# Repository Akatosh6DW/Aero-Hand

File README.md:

<p align="center">

  <!--  -->

</p>

Aero Hand Open is an **open-source**, **tendon-driven** robotic hand designed and developed by TetherIA for dexterous manipulation research. Unlike expensive proprietary solutions, this hand focuses on **simplicity**, **reliability**, and **accessibility** by using standard 3D printing and off-the-shelf electronic components.

Each joint is optimized for mechanical efficiency through tendon actuation, enabling smooth and natural motion while maintaining a **lightweight** and **compact** design, making it perfect for research labs, educational institutions, and robotics enthusiasts who need an **affordable** yet **capable** manipulation platform.

> **📚 Learn More:** https://tetheria.github.io/aero-hand-open/   
> **🛒 Shop:** https://shop.tetheria.ai/

# Aero Hand Open features
- 7 DoFs robotic hand with 5 fingers (16 joints in total)
- Tendon-driven architecture for smooth and natural motion
- Fully 3D-printed structure, modular and easy to assemble
- Lightweight design — **389 g**
- Affordable — complete kit for **$314 USD**
- Open-source hardware and firmware
- Independent Python SDK, and compatible with ESP32 and ROS2 systems

# Table of Contents
- [Aero Hand Open features](#aero-hand-open-features)
- [Overview](#overview)
- [Resources](#resources)
  - [Bill of Materials (BOM)](#bill-of-materials-bom)
  - [CAD Files and 3D Models](#cad-files-and-3d-models)
  - [Assembly Guide](#assembly-guide)
  - [PCB Design](#pcb-design)
  - [Hardware Setup](#hardware-setup)
  - [Software SDK](#software-sdk)
  - [ROS2 and Teleoperation](#ros2-and-teleoperation)
  - [Simulation](#simulation)
  - [Reinforcement Learning](#reinforcement-learning-tools)
- [Getting help](#Getting-help)
- [License — TL;DR](#license--tldr)
- [Disclaimer](#disclaimer)
- [Project Updates & Community](#project-updates--community)
  - [Updates History](#updates-history)
  - [FAQ](#faq)
  - [Contact](#contact)

# Overview

# Resources
## Bill of Materials (BOM)
The complete list of components required to build Aero Hand Open can be found here:

 [👉 Aero Hand Open – Bill of Materials](./hardware/Assembly/BOM.csv)

This document includes all mechanical, electronic, and printed parts — such as motors, tendons, bearings, fasteners, and 3D-printed components.

Each item is listed with its part number, vendor, quantity, and estimated cost to help you easily source or substitute parts.

## CAD Files and 3D Models
STEP files and one click print files can be found here:

[👉 Aero Hand Open – CAD](./hardware/CAD/).

[👉 Aero Hand Open – Onshape Link](https://cad.onshape.com/documents/afc7e0ca7eb6d412ec8771f8/w/bc4d7e45e17e23d622d2bad2/e/c711982b7882da925263fb55?renderMode=0&uiState=6914cef580110c73012e8166)

All parts are printed on a Bambu X1C, 0.4mm nozzle, 0.2mm layer height, tree support enabled, select support on build plate only checkbox. We recommend keeping the same print orientation and settings. The print orientation will minimize supports and optimize surface tolerances/smoothness for interfacing components.

## Assembly Guide
The step-by-step assembly instructions for Aero Hand Open are provided in the following document:

[👉 Aero Hand Open – Assembly Guide](https://docs.tetheria.ai/docs/assembly)

This guide covers the entire build process, from mounting the actuators to routing the tendons and connecting the electronics. Each finger module can be assembled independently and attached to the palm afterward, allowing easier maintenance and quick replacement.

## PCB Design
All design files - including Gerber files, KiCad project files, BOM, and CPL - are available in [PCB folder](./hardware/PCB/).

Referring to [PCB doc](https://docs.tetheria.ai/docs/pcb) for more technical details.

## Hardware Setup

Please refer to [hardware_setup](https://docs.tetheria.ai/docs/hardware_setup) doc 

## Software SDK
Please refer to [`sdk/README.md`](sdk/README.md) and [sdk](https://docs.tetheria.ai/docs/sdk) doc

### Sequencing Demo
The Sequencing Demo demonstrates how different finger motions can be combined into continuous, pre-defined sequences.

This script enables users to perform complex gestures — such as pinching, opening the palm, or making a peace sign — by automatically coordinating joint movements in a timed sequence.

You can find the example code in the SDK example folder. 

👉 [`sdk/examples/`](sdk/examples)

Once the SDK is installed and the serial port has been configured, you can run any of the example scripts directly using Python as follows:

```bash
python run_sequence.py
```
[🎥 Watch the demo](assets/sequence_square.mp4)

## ROS2 and Teleoperation
The Aero Hand Open integrates seamlessly with ROS2 **humble** for advanced robotics applications.

Refer to the [ROS2](https://docs.tetheria.ai/docs/ros2) doc and [`ros2/`](./ros2/) folder for complete setup instructions and source code.

## Simulation

We provide high-fidelity simulation models for the **Tetheria Aero Hand Open**.

**Currently Supported**
- **MuJoCo**

Support for additional simulation platforms is under active development and will be released in future updates.  
Refer to the [RL and Sim](https://docs.tetheria.ai/docs/hand_sim) documentation and the [`sim_rl/simulation/`](./sim_rl/simulation/) directory for detailed explanations and model files.

## Reinforcement Learning Tools

We offer reinforcement learning tools built on top of state-of-the-art frameworks such as **mujoco_playground**, enabling users to train custom policies for the Aero Hand Open with minimal effort.

Refer to the [RL and Sim](https://docs.tetheria.ai/docs/hand_sim) documentation and the [`sim_rl/mujoco_playground/`](./sim_rl/mujoco_playground/) directory for full setup instructions and training procedures.  
An example of deploying trained policies in ROS is also provided in the [`ros2/`](./ros2/) directory.

# Getting help

**GitHub Issues** – Bugs + feature requests only.

**GitHub Discussions** –
- Build / electronics / mechanical help
- SDK / ROS2 / sim/RL "how do I…"
- Design proposals and feedback

**Discord** –
- Quick questions, live debugging, voice/screen‑share
- Social chat, lab intros, "I printed my first hand!"
- Live events and office hours

# License — TL;DR

- You **can** integrate Aero Hand units you purchase from TetherIA into **commercial robots and products** you sell.
- **Software (firmware & SDK):** Apache-2.0 — commercial use OK (with notices).
- **Design files (CAD/STEP/STL, drawings, BOM, docs):** CC BY‑NC‑SA 4.0 — **non‑commercial** only; derivatives must use the same license with attribution.
- Want to **manufacture/print parts** or **make your own hands** from our design files for commercial use (spares, kits, or clones)? → **Commercial manufacturing license required**.
- **Commercial licensing & volume buys:** see **LICENSE.md** (or email us at contact@tetheria.ai).

See [**LICENSE.md**](LICENSE.md) for definitions, examples, and contact details.

© 2025 TetherIA Inc. All rights reserved.

# Disclaimer
Aero Hand Open is an open-source research prototype intended for educational and experimental purposes only.

While every effort has been made to ensure build accuracy and functionality, this design has not been validated for prolonged or heavy-duty use.

Users should exercise caution when assembling, operating, or modifying this device. TetherIA Inc. and its contributors shall not be held liable for any personal injury, property damage, or other losses resulting from the use, misuse, or modification of this design. By using this project, you acknowledge and accept full responsibility for any associated risks.

Important Notes:
- 3D-printed parts may exhibit tolerance variations depending on printer and material settings.
- The tendon-driven mechanism requires regular tension adjustment to maintain consistent motion.
- Overloading the joints or applying excessive torque may cause mechanical deformation or servo damage.
- This project is provided as is, without any warranty or guarantee of fitness for a particular purpose.

We encourage the community to share improvements, feedback, and modifications through pull requests or GitHub discussions.

Your contributions will help make Aero Hand Open more reliable and versatile for the entire robotics community.

# Project Updates & Community
## Updates History
- 11/7/2025
  - Version 1.0.0 release
- 10/24/2025
  - Release hardware and ROS2 packages
- 10/13/2025
  - Product launched on all platforms

## FAQ
Q1: Can I modify and redistribute the Aero Hand Open design?

A: Yes, as long as it complies with the CC BY-NC-SA 4.0 license (non-commercial, attribution required, share alike).

Q2: What 3D printer and material do you recommend?

A: Any FDM printer with a ≥200×200 mm bed. PLA works best for strength and dimensional accuracy.

## Contact
For questions, feedback, or collaboration inquiries, please reach out to us through the following channels:

 🛒 Shop: [Aero Hand Open – TetherIA Store](https://shop.tetheria.ai/) 

 📚 Docs: [TetherIA Docs](https://docs.tetheria.ai/)

 📧 Email: support@tetheria.ai

 🌐 Website: [tetheria.ai](http://tetheria.ai)

 🐙 GitHub: [TetherIA](https://github.com/TetherIA)

 💬 Discord: [TetherIA Discord Channel](http://discord.gg/ZQKWK7NebQ)

  🐦 X/Twitter: [TetherIA X/Twitter Account](https://x.com/TetherIA_ai)

  📺 YouTube: [TetherIA YouTube Account](https://www.youtube.com/@TetherIA_ai)

  💼 LinkedIn: [TetherIA LinkedIn Account](https://www.linkedin.com/company/tetheria/)

We welcome discussions, contributions, and new ideas from the community.

If you have improvements to the design, firmware, or control software, feel free to open a Pull Request or start a Discussion on GitHub.

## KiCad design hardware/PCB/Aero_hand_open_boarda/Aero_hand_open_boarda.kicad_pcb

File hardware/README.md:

**License:** [CC BY-NC-SA 4.0](https://creativecommons.org/licenses/by-nc-sa/4.0/) © 2025 TetherIA

[**Mechanical**](https://docs.tetheria.ai/docs/mechanical)

[**Assembly**](https://docs.tetheria.ai/docs/assembly)

[**Hardware Setup**](https://docs.tetheria.ai/docs/hardware_setup)

[**PCB**](https://docs.tetheria.ai/docs/pcb)

[**Firmware**](https://docs.tetheria.ai/docs/firmware)

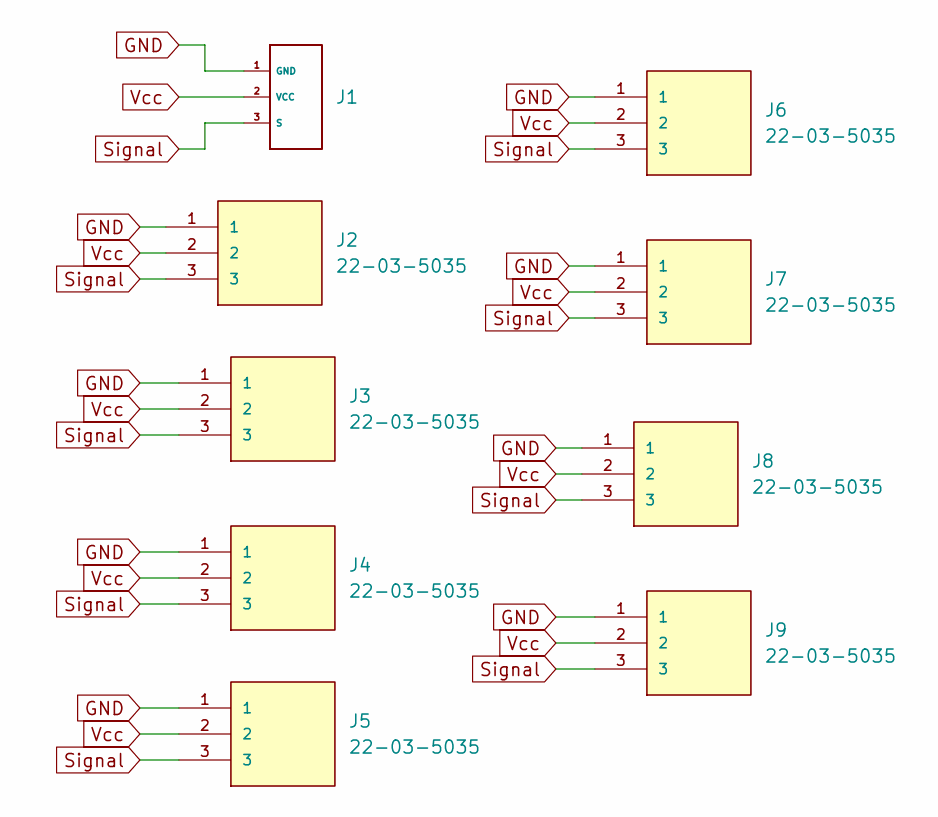
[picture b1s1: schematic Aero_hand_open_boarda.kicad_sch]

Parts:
J1: JST S3P-VH(LF)(SN)
J2, J3, J4, J5, J6, J7, J8, J9: 22-03-5035; MOLEX_22-03-5035; PARTREV B

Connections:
GND: J1.1 (GND), J2.1, J3.1, J4.1, J5.1, J6.1, J7.1, J8.1, J9.1
Signal: J1.3 (S), J2.3, J3.3, J4.3, J5.3, J6.3, J7.3, J8.3, J9.3
Vcc: J1.2 (VCC), J2.2, J3.2, J4.2, J5.2, J6.2, J7.2, J8.2, J9.2

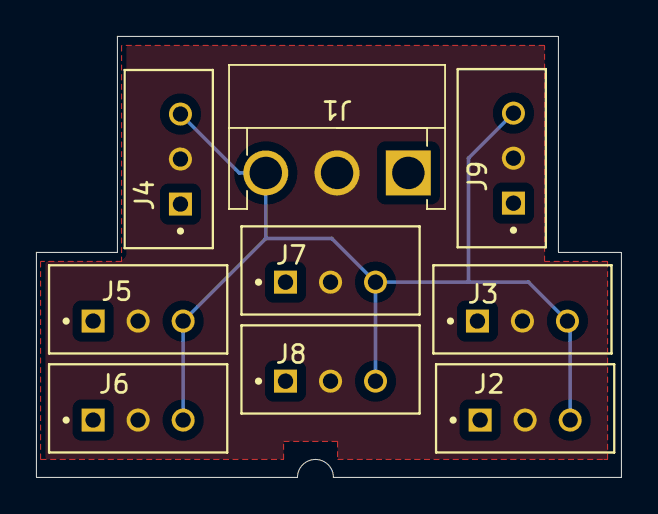
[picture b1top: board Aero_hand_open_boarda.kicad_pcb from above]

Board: 2 copper layers, 32.5 x 24.5 mm, 9 parts (0 on the bottom side), 3 nets.

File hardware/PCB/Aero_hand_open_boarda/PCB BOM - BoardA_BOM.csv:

Comment,Quantity,Designator,Footprint,JLCPCB Part,Link,,,,,,,,,,,,,,
MOLEX CONNECTOR,8,"J2,J3,J4,J5,J6,J7,J8,J9",MOLEX_22-03-5035,C293315,https://jlcpcb.com/partdetail/MOLEX-22035035/C293315?_gl=1%2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,,,,,,,,,,,,,,
JST 3 PIN CONNECTOR,1,J1,JST S3P-VH(LF)(SN),C264986,https://jlcpcb.com/partdetail/JST-S3P_VH_LF_SN/C264986,,,,,,,,,,,,,,

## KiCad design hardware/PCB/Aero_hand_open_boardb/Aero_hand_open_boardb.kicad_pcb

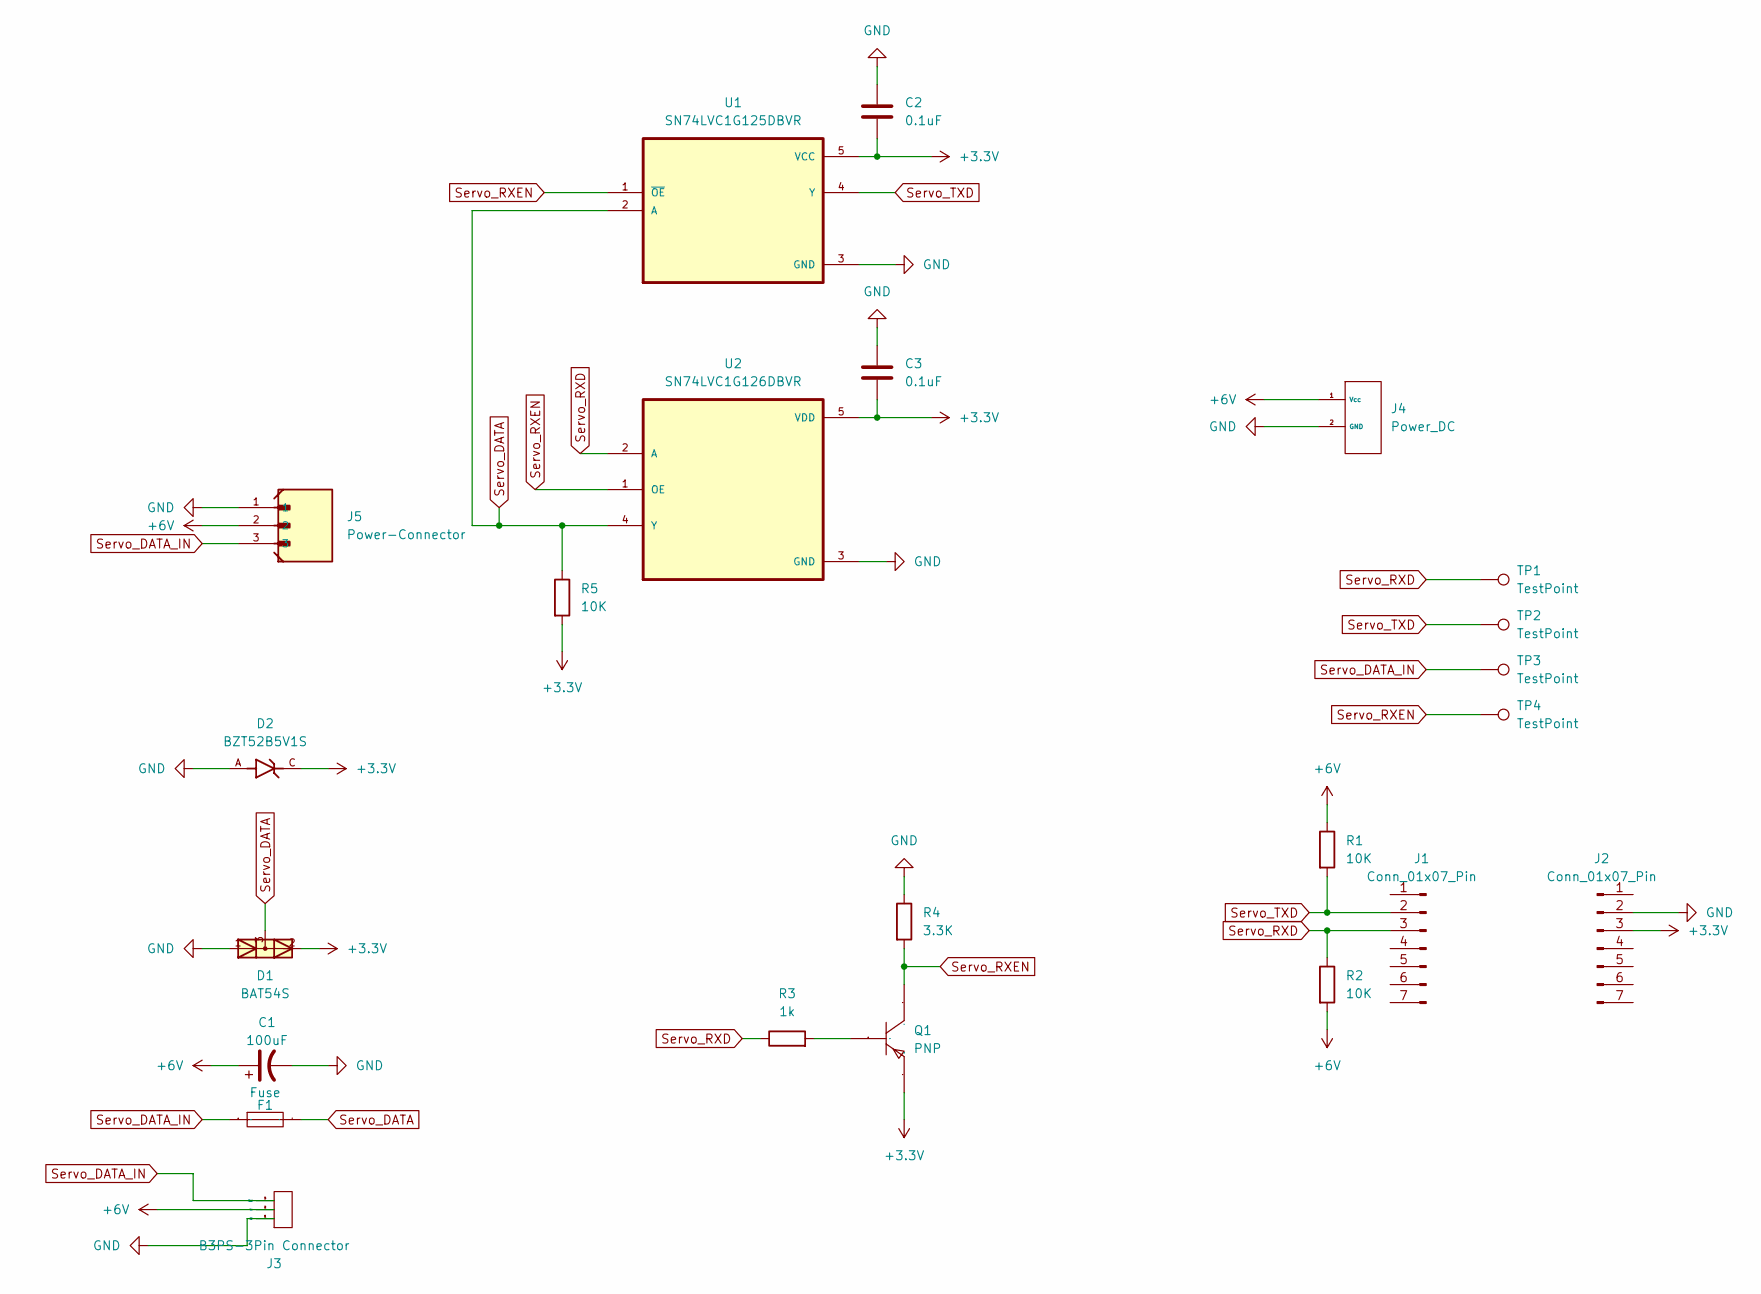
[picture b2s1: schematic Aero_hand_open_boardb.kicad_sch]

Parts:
C1: 100uF; CP_Radial_D5.0mm_P2.00mm
C2, C3: 0.1uF; C_0805
D1: BAT54S; SOT23
D2: BZT52B5V1S; DIO_BZT52B5V1S; PARTREV H2212
F1: Fuse; F0603; Manufacturer Part BSMD0603-010-24V; LCSC Part Name 24V 100mA 0603自恢复
J1, J2: Conn_01x07_Pin; PinHeader_1x07_P2.54mm_Vertical
J3: B3PS-3Pin Connector; JST S3P-VH(LF)(SN)
J4: Power_DC; KJ127-5.08
J5: Power-Connector; MOLEX_22057035; PARTREV A
Q1: PNP; SOT-23-3_L3.0-W1.7-P0.95-LS2.9-BR; Manufacturer Part MMBT2907A; LCSC Part Name MMBT2907A
R1, R2, R5: 10K; R_0805
R3: 1k; R_0805
R4: 3.3K; R_0805
TP1, TP2, TP3, TP4: TestPoint; TestPoint_Pad_D1.0mm
U1: SN74LVC1G125DBVR; SOT95P280X145-5N
U2: SN74LVC1G126DBVR; SOT95P280X145-5N; DigiKey_Part_Number 296-11605-1-ND

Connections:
+3.3V: C2.2, C3.2, D1.2, D2.C, J2.3, Q1.2 (E), R5.2, U1.5 (VCC), U2.5 (VDD)
+6V: C1.1, J3.2 (Vcc), J4.1 (Vcc), J5.2, R1.1, R2.2
GND: C1.2, C2.1, C3.1, D1.1, D2.A, J2.2, J3.1 (GND), J4.2 (GND), J5.1, R4.1, U1.3 (GND), U2.3 (GND)
unnamed: Q1.1 (B), R3.2
Servo_DATA: D1.3, F1.2, R5.1, U1.2 (A), U2.4 (Y)
Servo_DATA_IN: F1.1, J3.3 (Signal), J5.3, TP3.1
Servo_RXD: J1.3, R2.1, R3.1, TP1.1, U2.2 (A)
Servo_RXEN: Q1.3 (C), R4.2, TP4.1, U1.1 (~OE), U2.1 (OE)
Servo_TXD: J1.2, R1.2, TP2.1, U1.4 (Y)

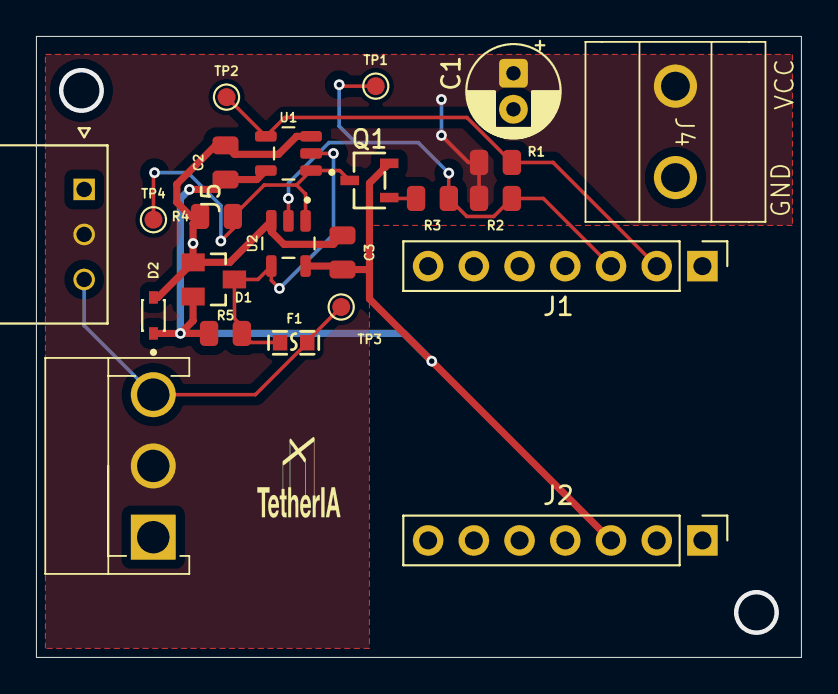
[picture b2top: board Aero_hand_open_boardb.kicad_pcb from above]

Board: 2 copper layers, 42.5 x 34.5 mm, 23 parts (1 on the bottom side), 9 nets.

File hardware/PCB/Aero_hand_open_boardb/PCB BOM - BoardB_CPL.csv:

Designator,Comment,Footprint,Mid X,Mid Y,Rotation,Layer,,,,,,,,,,,,,
C1,100uF,CP_Radial_D5.0mm_P2.00mm,26.5,-2.0449,-90,TOP,,,,,,,,,,,,,
C2,0.1uF,C_0805,10.5,-7,-90,TOP,,,,,,,,,,,,,
C3,0.1uF,C_0805,17,-12,-90,TOP,,,,,,,,,,,,,
D1,BAT54S,SOT23,9.85,-13.5,-90,TOP,,,,,,,,,,,,,
D2,BZT52B5V1S,DIO_BZT52B5V1S,6.5,-15.5,90,TOP,,,,,,,,,,,,,
F1,Fuse,F0603,14.29,-17.02,180,TOP,,,,,,,,,,,,,
J1,Conn_01x07_Pin_LeftESP,PinHeader_1x07_P2.54mm_Vertical,37,-12.76,-90,TOP,,,,,,,,,,,,,
J2,Conn_01x07_Pin_RightESP,PinHeader_1x07_P2.54mm_Vertical,37,-28,-90,TOP,,,,,,,,,,,,,
J4,Power_DC,KJ127-5.08,35.5,-5.3,-90,TOP,,,,,,,,,,,,,
Q1,PNP,SOT-23-3_L3.0-W1.7-P0.95-LS2.9-BR,18.5,-8,0,TOP,,,,,,,,,,,,,
R1,10K,R_0805,25.5,-7,0,TOP,,,,,,,,,,,,,
R2,10K,R_0805,25.5,-9,180,TOP,,,,,,,,,,,,,
R3,1k,R_0805,22,-9,180,TOP,,,,,,,,,,,,,
R4,3.3K,R_0805,10,-10,0,TOP,,,,,,,,,,,,,
R5,10K,R_0805,10.5,-16.5,180,TOP,,,,,,,,,,,,,
U1,SN74LVC1G125DBVR,SOT95P280X145-5N,14,-6.5,180,TOP,,,,,,,,,,,,,
U2,SN74LVC1G126DBVR,SOT95P280X145-5N,14,-11.5,-90,TOP,,,,,,,,,,,,,
J3,B3PS-3 Pin Connector JST,JST S3P-VH(LF)(SN),6.49,-23.36,-90,TOP,,,,,,,,,,,,,
J5,Right Angle 3P Molex Connector,22057035 MOLEX Right Angle Connector,2.65,-8.5--,-90,TOP,,,,,,,,,,,,,

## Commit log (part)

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2025-10-13 add the overall introduction
2025-10-13 changes per comments
2025-10-13 break the first paragraph into multiple paragraphs
2025-10-13 add line breaks
2025-10-13 add one more break
2025-10-13 git subrepo pull --branch=main firmware
    subrepo:
    subdir: "firmware"
    merged: "238ffc1"
    upstream:
    origin: "https://github.com/TetherIA/aero-open-firmware.git"
    branch: "main"
2025-10-13 git subrepo pull --branch=main hardware
    subrepo:
    subdir: "hardware"
    merged: "b968aa1"
    upstream:
    origin: "https://github.com/TetherIA/aero-open-hardware.git"
    branch: "main"
2025-10-13 git subrepo pull --branch=main sdk
    subrepo:
    subdir: "sdk"
    merged: "a3fcc29"
    upstream:
    origin: "https://github.com/TetherIA/aero-open-sdk.git"
    branch: "main"
2025-10-13 sync pull firmware and sdk via subrepo
2025-10-13 git subrepo pull --branch=main firmware
    subrepo:
    subdir: "firmware"
    merged: "46bc858"
    upstream:
    origin: "https://github.com/TetherIA/aero-open-firmware.git"
    branch: "main"
2025-10-14 doc imgs files
2025-10-14 revert hardware
2025-10-14 add readme
2025-10-14 remove gitattributes file
2025-10-14 git subrepo pull --branch=main sdk
    subrepo:
    subdir: "sdk"
    merged: "a3fcc29"
    upstream:
    origin: "https://github.com/TetherIA/aero-open-sdk.git"
    branch: "main"
2025-10-14 git subrepo pull --branch=main firmware
    subrepo:
    subdir: "firmware"
    merged: "46bc858"
    upstream:
    origin: "https://github.com/TetherIA/aero-open-firmware.git"
    branch: "main"
2025-10-14 Squashed 'docs/' changes from bced288..a0e21f6
    a0e21f6 fix sidebar issue (#14)
    92761e5 ADD: Software doc updated (#12)
    git-subtree-dir: docs
    git-subtree-split: a0e21f6054b498eb8d931e0a72b43fe87464bddc
2025-10-14 Auto sync/ind2mono 20251013 code (#5)
    * git subrepo pull --branch=main firmware
    subrepo:
    subdir: "firmware"
    merged: "46bc858"
    upstream:
    origin: "https://github.com/TetherIA/aero-open-firmware.git"
2025-10-14 add more hyperlinks
2025-10-14 change hyper link name
2025-10-14 use relative path
2025-10-14 Update README.md
    updated weight and printing instructions
2025-10-14 fix some typo
2025-10-14 update png
2025-10-14 Revert "fix some typo"
    This reverts commit 597434d3e9e65ba1d74abc1de1c980ee0750a6a0.
2025-10-14 Revert "update png"
    This reverts commit 3a05dff97819c69d0007711d7843f648de97d164.
2025-10-14 revert some weird changes
2025-10-14 Update README.md (#7)
    updated weight and printing instructions
2025-10-16 Fix license
2025-10-16 add hardware readme file
2025-10-16 15 joints -> 16 joints
2025-10-17 fix physical material
2025-10-17 cable -> tendon
2025-10-17 git subrepo clone --branch=public_release https://github.com/TetherIA/aero-open-ros2.git ros2
    subrepo:
    subdir: "ros2"
    merged: "8c87f05"
    upstream:
    origin: "https://github.com/TetherIA/aero-open-ros2.git"
    branch: "public_release"
2025-10-19 small readme fix
2025-10-20 small readme fix (#12)
2025-10-24 small fix
2025-10-24 update readme (#13)
    * update readme
    * small fix
    ---------
2025-10-24 git subrepo commit (merge) hardware
    subrepo:
    subdir: "hardware"
    merged: "852004f"
    upstream:
    origin: "https://github.com/TetherIA/aero-open-hardware.git"
    branch: "main"
2025-10-24 update discord link
2025-10-24 fix(subrepo): update parent after squash/rebase to 4f5a096a414a4a136db2a5e623b21e75ecf6ca96
2025-10-27 git subrepo pull --branch=main firmware
    subrepo:
    subdir: "firmware"
    merged: "d7bd82e"
    upstream:
    origin: "https://github.com/TetherIA/aero-open-firmware.git"
    branch: "main"
2025-10-27 git subrepo pull --branch=main sdk
    subrepo:
    subdir: "sdk"
    merged: "c5f5f8c"
    upstream:
    origin: "https://github.com/TetherIA/aero-open-sdk.git"
    branch: "main"
2025-10-27 git subrepo pull --branch=public_release ros2
    subrepo:
    subdir: "ros2"
    merged: "91b25ab"
    upstream:
    origin: "https://github.com/TetherIA/aero-open-ros2.git"
    branch: "public_release"
2025-10-27 Squashed 'docs/' changes from a0e21f6..9fe5d71
    9fe5d71 update discord link (#22)
    6bec897 added images and pcb document on repo and linked as well (#21)
    a3ca406 add torque related readme and small fixes (#20)
    b2f9969 User/harsh/firmware (#19)
    2109234 Mohit/fix software doc (#17)
    f42a0e5 update social media links (#18)
2025-10-27 git subrepo pull (merge) --branch=main hardware
    subrepo:
    subdir: "hardware"
    merged: "41594a8"
    upstream:
    origin: "https://github.com/TetherIA/aero-open-hardware.git"
    branch: "main"
2025-10-27 Squashed 'docs/' changes from 9fe5d71..a404d8b
    a404d8b update assembly instruction (#23)
    git-subtree-dir: docs
    git-subtree-split: a404d8b800827d15a4cfc618c9a9260c1f748f98
2025-10-27 remove assembly file
2025-10-27 git subrepo pull --force --branch=public_release ros2
    subrepo:
    subdir: "ros2"
    merged: "73d07a5"
    upstream:
    origin: "https://github.com/TetherIA/aero-open-ros2.git"
    branch: "public_release"
2025-10-27 git subrepo pull --force --branch=public_release ros2
    subrepo:
    subdir: "ros2"
    merged: "394f14a"
    upstream:
    origin: "https://github.com/TetherIA/aero-open-ros2.git"
    branch: "public_release"
2025-10-27 Manual sync: individual → monorepo 20251027 (#18)
    * git subrepo commit (merge) hardware
    subrepo:
    subdir: "hardware"
    merged: "852004f"
    upstream:
    origin: "https://github.com/TetherIA/aero-open-hardware.git"
2025-10-29 Revise README with new sections and links
    Updated the README to include new sections on mechanical, assembly, hardware setup, PCB, and firmware, along with relevant links.
2025-10-30 Update readme (#21)
2025-11-03 Fix formatting of links in README.md
2025-11-03 add contribute guidelines and remove CAD related stuff in readme
2025-11-04 add contribute guidelines and remove CAD related stuff in readme (#24)
2025-11-04 Fix formatting of links in README.md (#23)
2025-11-04 update bibtex
2025-11-04 add task videos
2025-11-04 make Video Gallery as carousel
2025-11-04 update video-carousel width
2025-11-04 update video-gallery size
2025-11-04 small updates
2025-11-04 adjust video-gallery-hero orders
2025-11-04 update DOF
2025-11-04 fix(subrepo): update parent after squash/rebase
2025-11-04 git subrepo pull --branch=main firmware
    subrepo:
    subdir: "firmware"
    merged: "39f0fff"
    upstream:
    origin: "https://github.com/TetherIA/aero-open-firmware.git"
    branch: "main"
2025-11-04 git subrepo pull --branch=main sdk
    subrepo:
    subdir: "sdk"
    merged: "00c8ea8"
    upstream:
    origin: "https://github.com/TetherIA/aero-open-sdk.git"
    branch: "main"
2025-11-04 git subrepo pull --branch=public_release ros2
    subrepo:
    subdir: "ros2"
    merged: "d4283ae"
    upstream:
    origin: "https://github.com/TetherIA/aero-open-ros2.git"
    branch: "public_release"
2025-11-04 remove docs folder
2025-11-04 Auto-sync/ind2mono-20251103 (#25)
    * fix(subrepo): update parent after squash/rebase
    * git subrepo pull --branch=main firmware
    subrepo:
    subdir: "firmware"
    merged: "39f0fff"
    upstream:
2025-11-04 Update RL policy
2025-11-04 fix rl videos display
2025-11-07 Update speed section
2025-11-07 git subrepo pull --branch=main --force hardware
    subrepo:
    subdir: "hardware"
    merged: "1b1b0f0"
    upstream:
    origin: "https://github.com/TetherIA/aero-open-hardware.git"
    branch: "main"
2025-11-07 simplify readme
2025-11-07 update hardware (for latest pcb) and simplify readme (#26)
    * git subrepo pull --branch=main --force hardware
    subrepo:
    subdir: "hardware"
    merged: "1b1b0f0"
    upstream:
    origin: "https://github.com/TetherIA/aero-open-hardware.git"
2025-11-12 Revise CAD files section in README
    Updated CAD file availability and printing recommendations.
2025-11-12 Clarify printing settings in README
    Updated printing instructions for clarity and accuracy.
2025-11-12 FIX: repo parent commit hash updated
2025-11-12 Fix typo in CAD files section of README
2025-11-12 git subrepo commit (merge) hardware
    subrepo:
    subdir: "hardware"
    merged: "ec9e8ea"
    upstream:
    origin: "https://github.com/TetherIA/aero-open-hardware.git"
    branch: "main"
2025-11-12 DELETE: old hardware files
2025-11-12 git subrepo clone --branch=main https://github.com/TetherIA/aero-open-hardware.git hardware
    subrepo:
    subdir: "hardware"
    merged: "43ab47d"
    upstream:
    origin: "https://github.com/TetherIA/aero-open-hardware.git"
    branch: "main"
2025-11-12 FIX: spell fix in CSV
2025-11-13 update license example
2025-11-13 Update cycle test and webcam teleop
2025-11-17 Add mujoco_playground_pr and aero-hand-open-sim as submodules
2025-11-18 Reorganize submodules into sim_rl/
2025-11-18 Update simulation submodule URL to TetherIA/aero-open-sim
2025-11-18 update links
2025-11-24 add getting help section
2025-11-25 add getting help section (#35)
2025-11-25 Update mujoco_playground submodule to google-deepmind upstream
2025-12-10 update firmware gitrepo file
2025-12-10 git subrepo pull --branch=main firmware
    subrepo:
    subdir: "firmware"
    merged: "79b2d72"
    upstream:
    origin: "https://github.com/TetherIA/aero-open-firmware.git"
    branch: "main"
2025-12-10 update sdk gitrepo file
2025-12-10 git subrepo pull --branch=main sdk
    subrepo:
    subdir: "sdk"
    merged: "a025960"
    upstream:
    origin: "https://github.com/TetherIA/aero-open-sdk.git"
    branch: "main"
2025-12-10 update ros2 gitrepo
2025-12-11 ros2 changes
2025-12-11 remove aero hand demo package under ros2 folder
2026-01-21 init version of release notes
2026-01-21 Fix subrepo parent after rebase
2026-01-21 git subrepo pull --branch=main firmware
    subrepo:
    subdir: "firmware"
    merged: "6abb5b3"
    upstream:
    origin: "https://github.com/TetherIA/aero-open-firmware.git"
    branch: "main"
2026-01-21 git subrepo pull (merge) --branch=main hardware
    subrepo:
    subdir: "hardware"
    merged: "27a6acc"
    upstream:
    origin: "https://github.com/TetherIA/aero-open-hardware.git"
    branch: "main"
2026-01-21 git subrepo pull --branch=main sdk
    subrepo:
    subdir: "sdk"
    merged: "8e1c9ca"
    upstream:
    origin: "https://github.com/TetherIA/aero-open-sdk.git"
    branch: "main"
2026-01-21 Fix ros2 subrepo parent after rebase
2026-01-21 git subrepo pull --branch=public_release --force ros2
    subrepo:
    subdir: "ros2"
    merged: "26392bf"
    upstream:
    origin: "https://github.com/TetherIA/aero-open-ros2.git"
    branch: "public_release"
2026-01-21 update release notes and readme
2026-01-21 polish release notes
2026-01-21 git subrepo pull --branch=public_release ros2
    subrepo:
    subdir: "ros2"
    merged: "f59855b"
    upstream:
    origin: "https://github.com/TetherIA/aero-open-ros2.git"
    branch: "public_release"
2026-01-22 Firmware v0.1.3 release note
2026-01-22 git subrepo pull --branch=main firmware
    subrepo:
    subdir: "firmware"
    merged: "6e21db4"
    upstream:
    origin: "https://github.com/TetherIA/aero-open-firmware.git"
    branch: "main"
2026-01-22 Auto-sync/ind2mono-20260120 (#38)
    * init version of release notes
    * Fix subrepo parent after rebase
    * git subrepo pull --branch=main firmware
    subrepo:
    subdir: "firmware"
    merged: "6abb5b3"
2026-01-22 fix sim_rl instructions and install
2026-01-26 fix sim_rl instructions and install (#39)
2026-03-02 配置.gitignore，屏蔽虚拟环境与缓存文件
2026-03-02 配置完成
2026-03-03 配置完成2
2026-03-05 引入更改后的手部模型
2026-03-08 转动方块完成版本
2026-03-08 转动方块完成
2026-03-21 可用于抓取的模型文件，以及可通过view.py快速查看模型文件
2026-03-21 无内容？
2026-03-21 完成抓取任务
2026-03-29 硬件部署初步完成，但缺少力反馈
2026-04-04 检测出力反馈有bug
2026-04-06 力反馈加入，初步效果完成
2026-04-08 隐式力反馈
2026-04-10 力加入状态空间，概率抓取30s
2026-04-16 全握瓶颈
2026-04-20 外部小扰动成功对握加扰动可视化
2026-04-20 夹方块稳定性高
2026-04-20 合并子模块到主仓库
2026-04-21 Add DR robustness updates and C30 training logs
2026-04-21 修复了生成视频的bug（存疑）
2026-04-22 瓶子抓取任务完成
2026-04-22 视频生成修复
2026-04-22 接触到瓶子
2026-04-22 接触到瓶子（含log)
2026-04-22 接触到瓶子（含log）
2026-04-22 抓取瓶子任务更改为抓取小圆柱
2026-04-23 瓶子22.5s
2026-04-23 检查出瓶子22.5s完全是错误的
2026-04-24 codex额度用完
2026-04-24 含记忆提示词
2026-04-25 抓取罐子未完成
2026-04-28 抓取方块修正不完全+罐子失败
